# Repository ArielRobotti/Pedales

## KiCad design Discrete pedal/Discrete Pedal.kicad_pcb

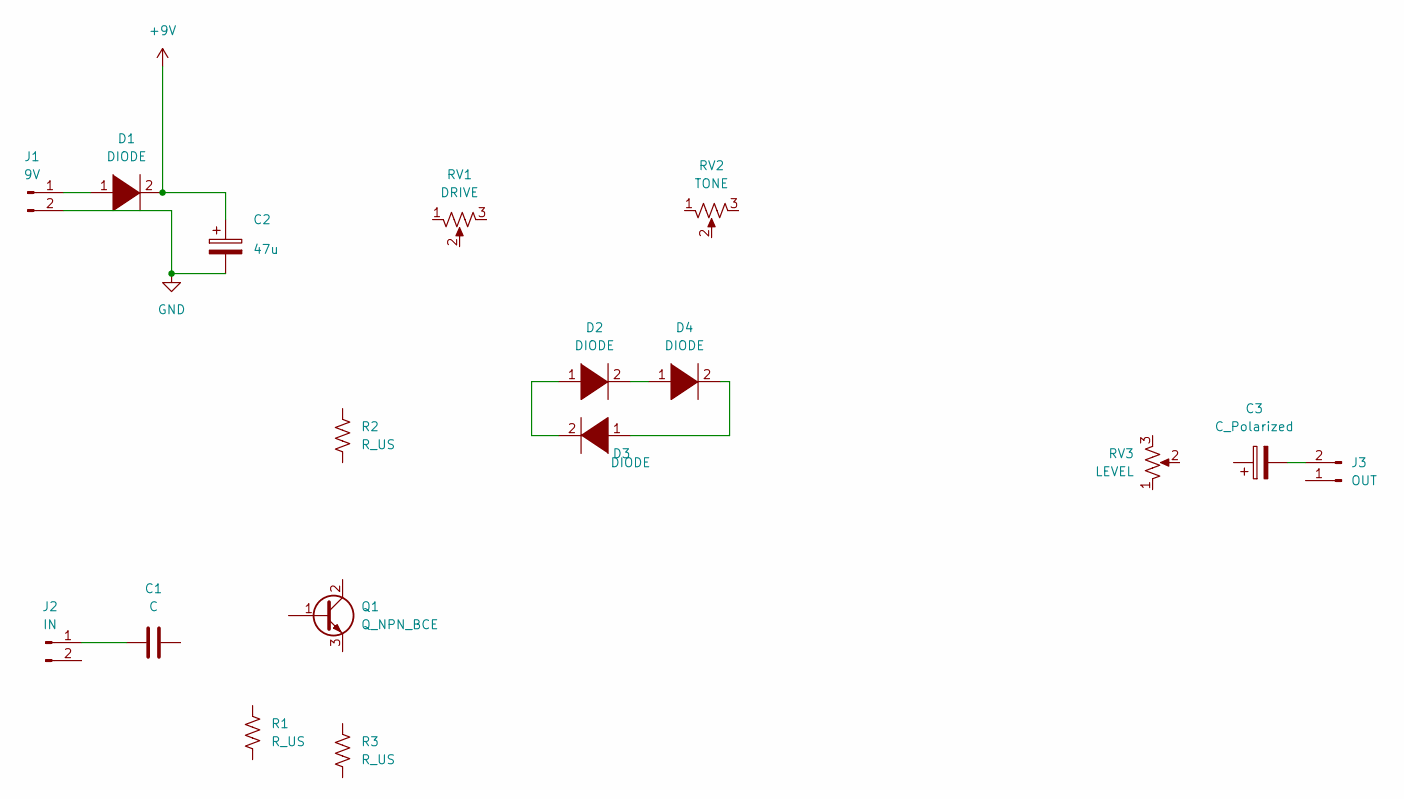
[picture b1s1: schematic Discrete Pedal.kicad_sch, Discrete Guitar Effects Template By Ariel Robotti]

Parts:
C1: C; C_0805_2012Metric
C2: 47u; CP_Elec_3x5.4
C3: C_Polarized; CP_Elec_3x5.4
D1: DIODE; D_1206_3216Metric
D2, D3, D4: DIODE; D_0805_2012Metric_Pad1.15x1.40mm_HandSolder
J1: 9V; PinHeader_1x02_P2.54mm_Vertical
J2: IN; PinHeader_1x02_P2.54mm_Vertical
J3: OUT; PinHeader_1x02_P2.54mm_Vertical
Q1: Q_NPN_BCE; SOT-23
R1, R2, R3: R_US; R_0805_2012Metric_Pad1.20x1.40mm_HandSolder
RV1: DRIVE; PinHeader_1x03_P2.54mm_Vertical
RV2: TONE; PinHeader_1x03_P2.54mm_Vertical
RV3: LEVEL; PinHeader_1x03_P2.54mm_Vertical

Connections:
+9V: C2.1, D1.2 (A)
GND: C2.2, J1.2
unnamed: C1.1, J2.1
unnamed: C3.2, J3.2
unnamed: D1.1 (K), J1.1
unnamed: D2.1 (K), D3.2 (A)
unnamed: D2.2 (A), D4.1 (K)
unnamed: D3.1 (K), D4.2 (A)

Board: 2 copper layers, 17 parts (0 on the bottom side), 8 nets, no tracks yet.

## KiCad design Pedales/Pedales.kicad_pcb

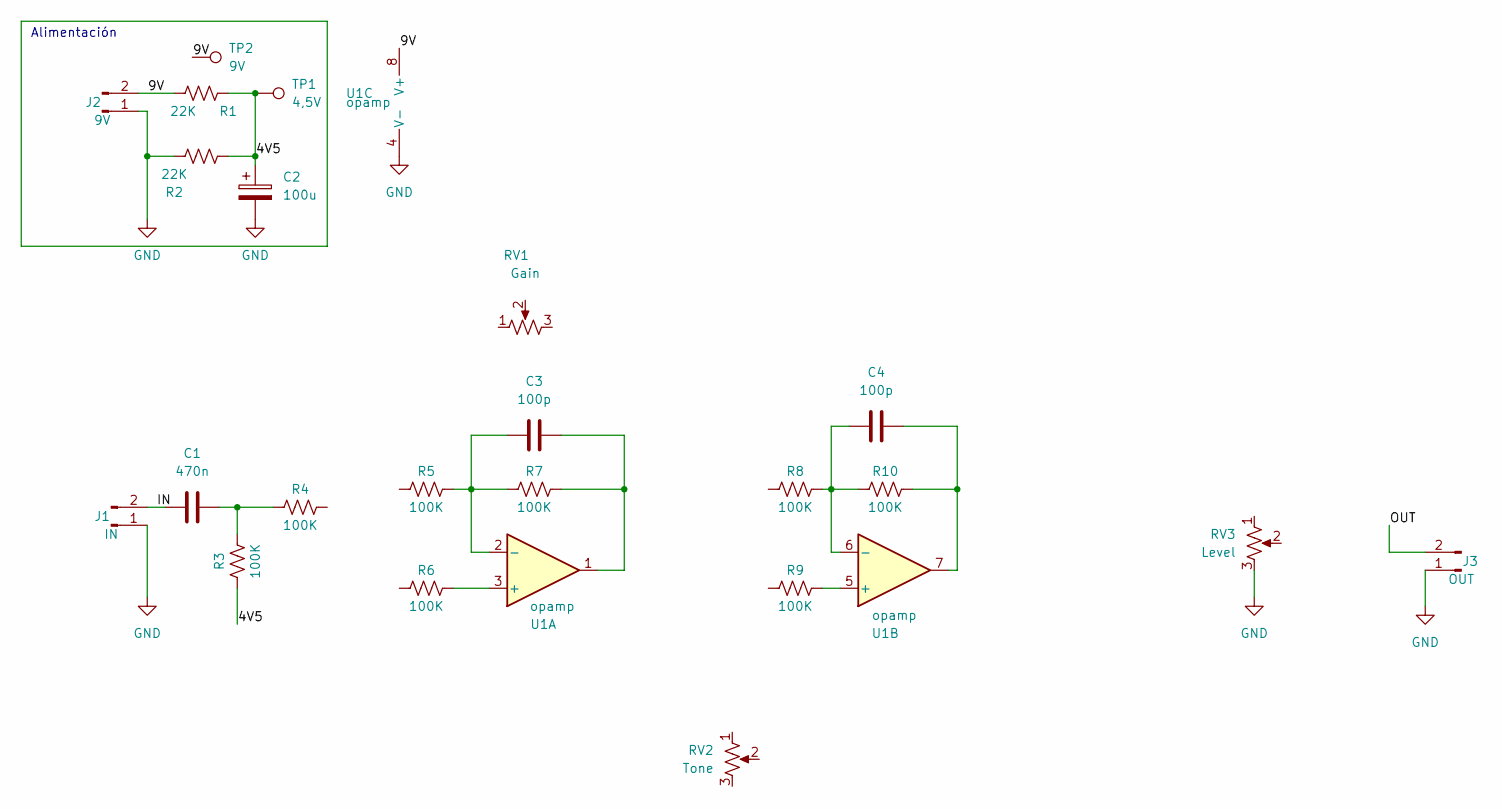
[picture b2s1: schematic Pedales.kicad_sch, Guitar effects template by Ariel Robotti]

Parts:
C1: 470n; C_0805_2012Metric
C2: 100u; CP_Elec_4x5.8
C3, C4: 100p; C_0805_2012Metric
J1: IN; PinHeader_1x02_P2.54mm_Vertical
J2: 9V; PinHeader_1x02_P2.54mm_Vertical
J3: OUT; PinHeader_1x02_P2.54mm_Vertical
R1, R2: 22K; R_0805_2012Metric_Pad1.20x1.40mm_HandSolder
R3, R4, R5, R6, R7, R8, R9, R10: 100K; R_0805_2012Metric_Pad1.20x1.40mm_HandSolder
RV1: Gain; PinHeader_1x03_P2.54mm_Vertical
RV2: Tone; PinHeader_1x03_P2.54mm_Vertical
RV3: Level; PinHeader_1x03_P2.54mm_Vertical
TP1: 4,5V; TestPoint_Pad_D1.5mm
TP2: 9V; TestPoint_Pad_D1.5mm
U1: opamp

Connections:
/4V5: C2.1, R1.2, R2.2, R3.1, TP1.1
/9V: J2.2, R1.1, TP2.1, U1.8 (V+)
/IN: C1.1, J1.2
/OUT: J3.2
GND: C2.2, J1.1, J2.1, J3.1, R2.1, RV3.3, U1.4 (V-)
unnamed: C1.2, R3.2, R4.1
unnamed: C3.1, R5.2, R7.1, U1.2 (-)
unnamed: C3.2, R7.2, U1.1
unnamed: C4.1, R8.2, R10.1, U1.6 (-)
unnamed: C4.2, R10.2, U1.7
unnamed: R6.2, U1.3 (+)
unnamed: R9.2, U1.5 (+)

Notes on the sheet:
Alimentación

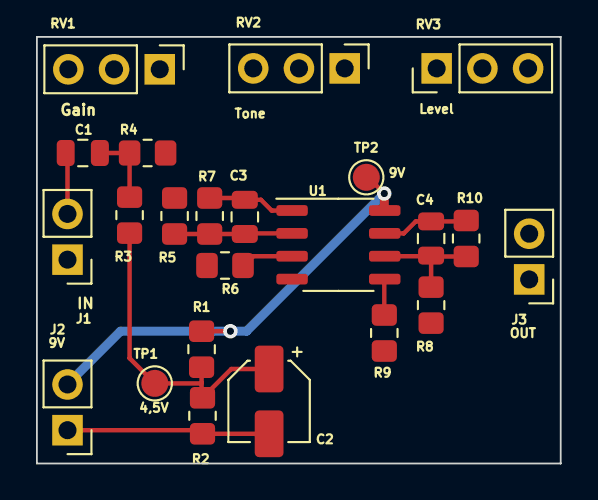
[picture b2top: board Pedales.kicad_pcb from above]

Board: 2 copper layers, 29.1 x 23.7 mm, 23 parts (0 on the bottom side), 11 nets.
